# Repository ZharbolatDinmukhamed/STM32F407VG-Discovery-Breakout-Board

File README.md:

# STM32F407VG-Discovery-Breakout-Board

A shield-style adapter/breakout board for the STM32F407VG-Disc1 (Discovery) board, designed and assembled at the Tactile Laboratory, Nazarbayev University.

## Overview

This board plugs directly onto the Discovery board's P1/P2 headers and breaks out all 100 GPIO pins to individual screw terminals, making it easy to wire external hardware to the STM32F407VG without soldering directly onto the Discovery board.

## Design Details

- **Form factor:** Shield-style board, mates directly with the Discovery board's P1/P2 headers
- **Pin breakout:** All 100 pins broken out to individual screw terminals
- **Assembly:** Designed, fabricated, and hand-soldered end-to-end

## Files

- `/schematic` — Schematic source files
- `/pcb` — PCB layout files
- `/gerbers` — Fabrication-ready Gerber files
- `/images` — Board renders and photos of the assembled, soldered board

## Tools

- KiCad

## Status

Assembled and soldered

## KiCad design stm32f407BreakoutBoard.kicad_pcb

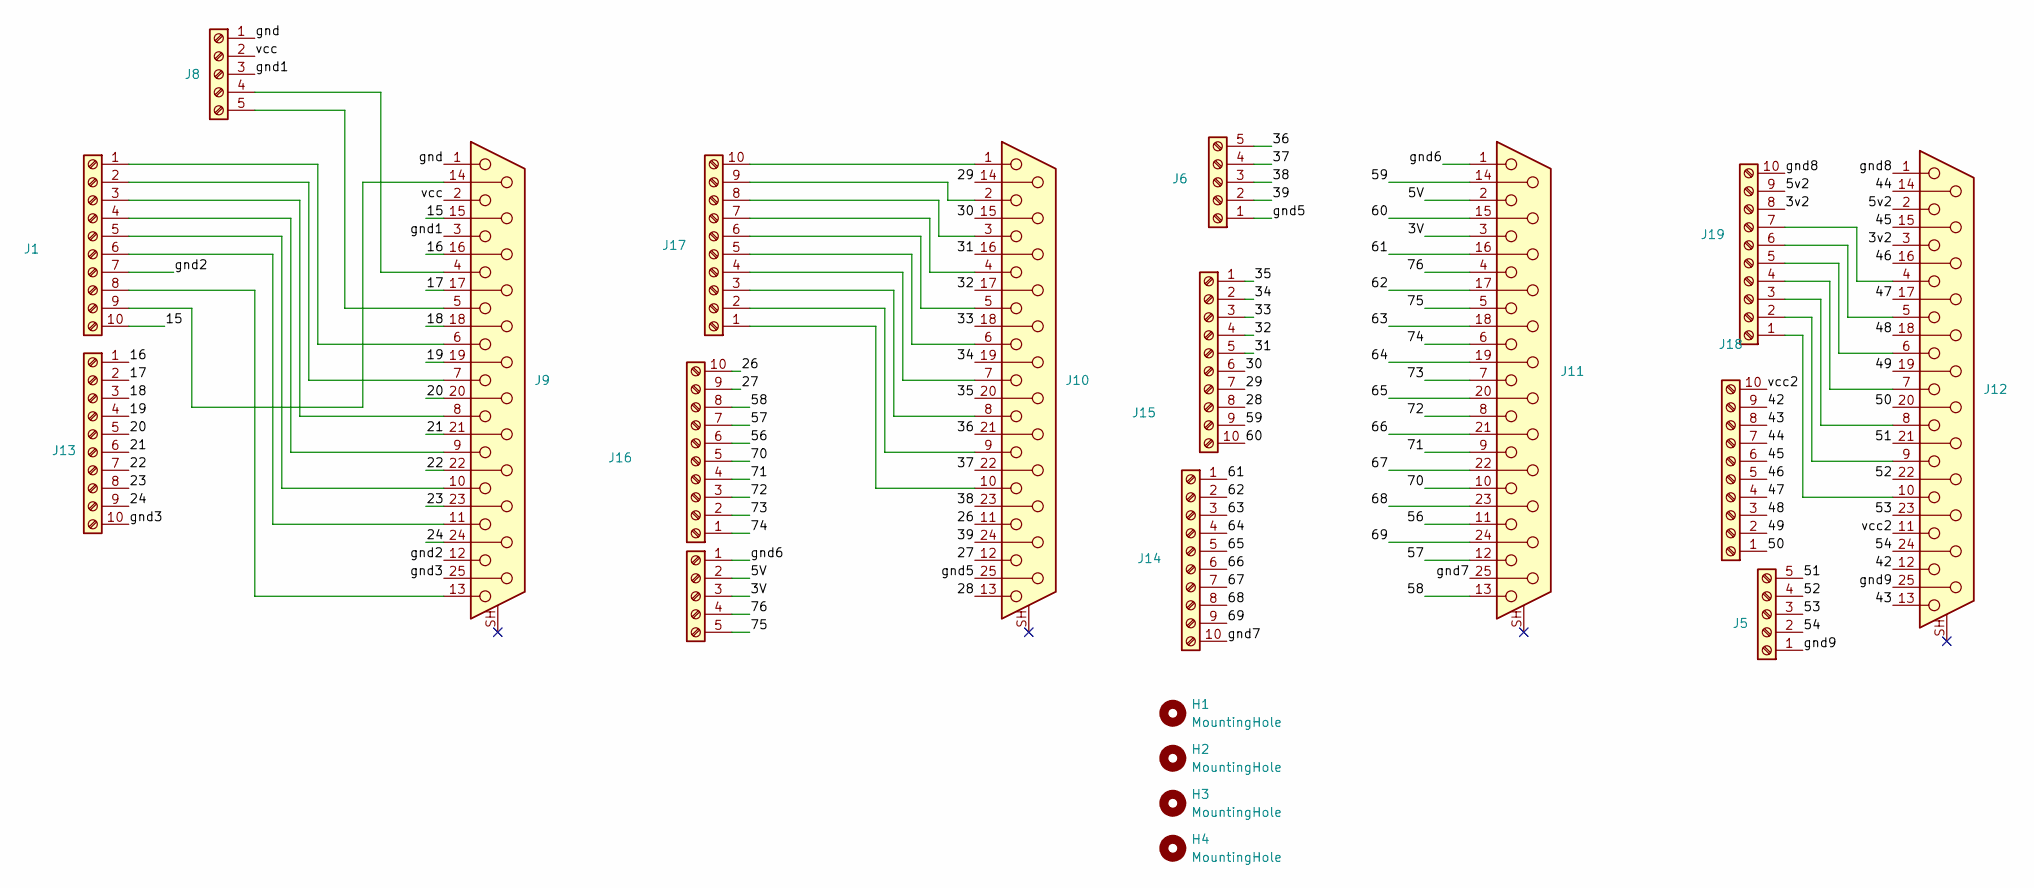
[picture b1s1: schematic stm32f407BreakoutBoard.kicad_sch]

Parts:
H1, H2, H3, H4: MountingHole; MountingHole_3.2mm_M3
J1, J13, J14, J15, J16, J17, J18, J19: Screw_Terminal_01x10; TerminalBlock_Phoenix_MKDS-1,5-10-5.08_1x10_P5.08mm_Horizon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
J5, J6, J7, J8: Screw_Terminal_01x05; TerminalBlock_Phoenix_MKDS-1,5-5-5.08_1x05_P5.08mm_Horizont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
J9, J10, J11, J12: DB25_Socket_MountingHoles; PinSocket_1x25_P2.54mm_Vertical

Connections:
/3V: J7.3, J11.3
/3v2: J12.3, J19.8
/5V: J7.2, J11.2
/5v2: J12.2, J19.9
/15: J1.10, J9.15
/16: J9.16, J13.1
/17: J9.17, J13.2
/18: J9.18, J13.3
/19: J9.19, J13.4
/20: J9.20, J13.5
/21: J9.21, J13.6
/22: J9.22, J13.7
/23: J9.23, J13.8
/24: J9.24, J13.9
/26: J10.11, J16.10
/27: J10.12, J16.9
/28: J10.13, J15.8
/29: J10.14, J15.7
/30: J10.15, J15.6
/31: J10.16, J15.5
/32: J10.17, J15.4
/33: J10.18, J15.3
/34: J10.19, J15.2
/35: J10.20, J15.1
/36: J6.5, J10.21
/37: J6.4, J10.22
/38: J6.3, J10.23
/39: J6.2, J10.24
/42: J12.12, J18.9
/43: J12.13, J18.8
/44: J12.14, J18.7
/45: J12.15, J18.6
/46: J12.16, J18.5
/47: J12.17, J18.4
/48: J12.18, J18.3
/49: J12.19, J18.2
/50: J12.20, J18.1
/51: J5.5, J12.21
/52: J5.4, J12.22
/53: J5.3, J12.23
/54: J5.2, J12.24
/56: J11.11, J16.6
/57: J11.12, J16.7
/58: J11.13, J16.8
/59: J11.14, J15.9
/60: J11.15, J15.10
/61: J11.16, J14.1
/62: J11.17, J14.2
/63: J11.18, J14.3
/64: J11.19, J14.4
/65: J11.20, J14.5
/66: J11.21, J14.6
/67: J11.22, J14.7
/68: J11.23, J14.8
/69: J11.24, J14.9
/70: J11.10, J16.5
/71: J11.9, J16.4
/72: J11.8, J16.3
/73: J11.7, J16.2
/74: J11.6, J16.1
/75: J7.5, J11.5
/76: J7.4, J11.4
/gnd: J8.1, J9.1
/gnd1: J8.3, J9.3
/gnd2: J1.7, J9.12
/gnd3: J9.25, J13.10
/gnd5: J6.1, J10.25
/gnd6: J7.1, J11.1
/gnd7: J11.25, J14.10
/gnd8: J12.1, J19.10
/gnd9: J5.1, J12.25
/vcc: J8.2, J9.2
/vcc2: J12.11, J18.10
unnamed: J1.1, J9.6
unnamed: J1.2, J9.7
unnamed: J1.3, J9.8
unnamed: J1.4, J9.9
unnamed: J1.5, J9.10
unnamed: J1.6, J9.11
unnamed: J1.8, J9.13
unnamed: J1.9, J9.14
unnamed: J8.4, J9.4
unnamed: J8.5, J9.5
unnamed: J10.10, J17.1
unnamed: J10.9, J17.2
unnamed: J10.8, J17.3
unnamed: J10.7, J17.4
unnamed: J10.6, J17.5
unnamed: J10.5, J17.6
unnamed: J10.4, J17.7
unnamed: J10.3, J17.8
unnamed: J10.2, J17.9
unnamed: J10.1, J17.10
unnamed: J12.10, J19.1
unnamed: J12.9, J19.2
unnamed: J12.8, J19.3
unnamed: J12.7, J19.4
unnamed: J12.6, J19.5
unnamed: J12.5, J19.6
unnamed: J12.4, J19.7

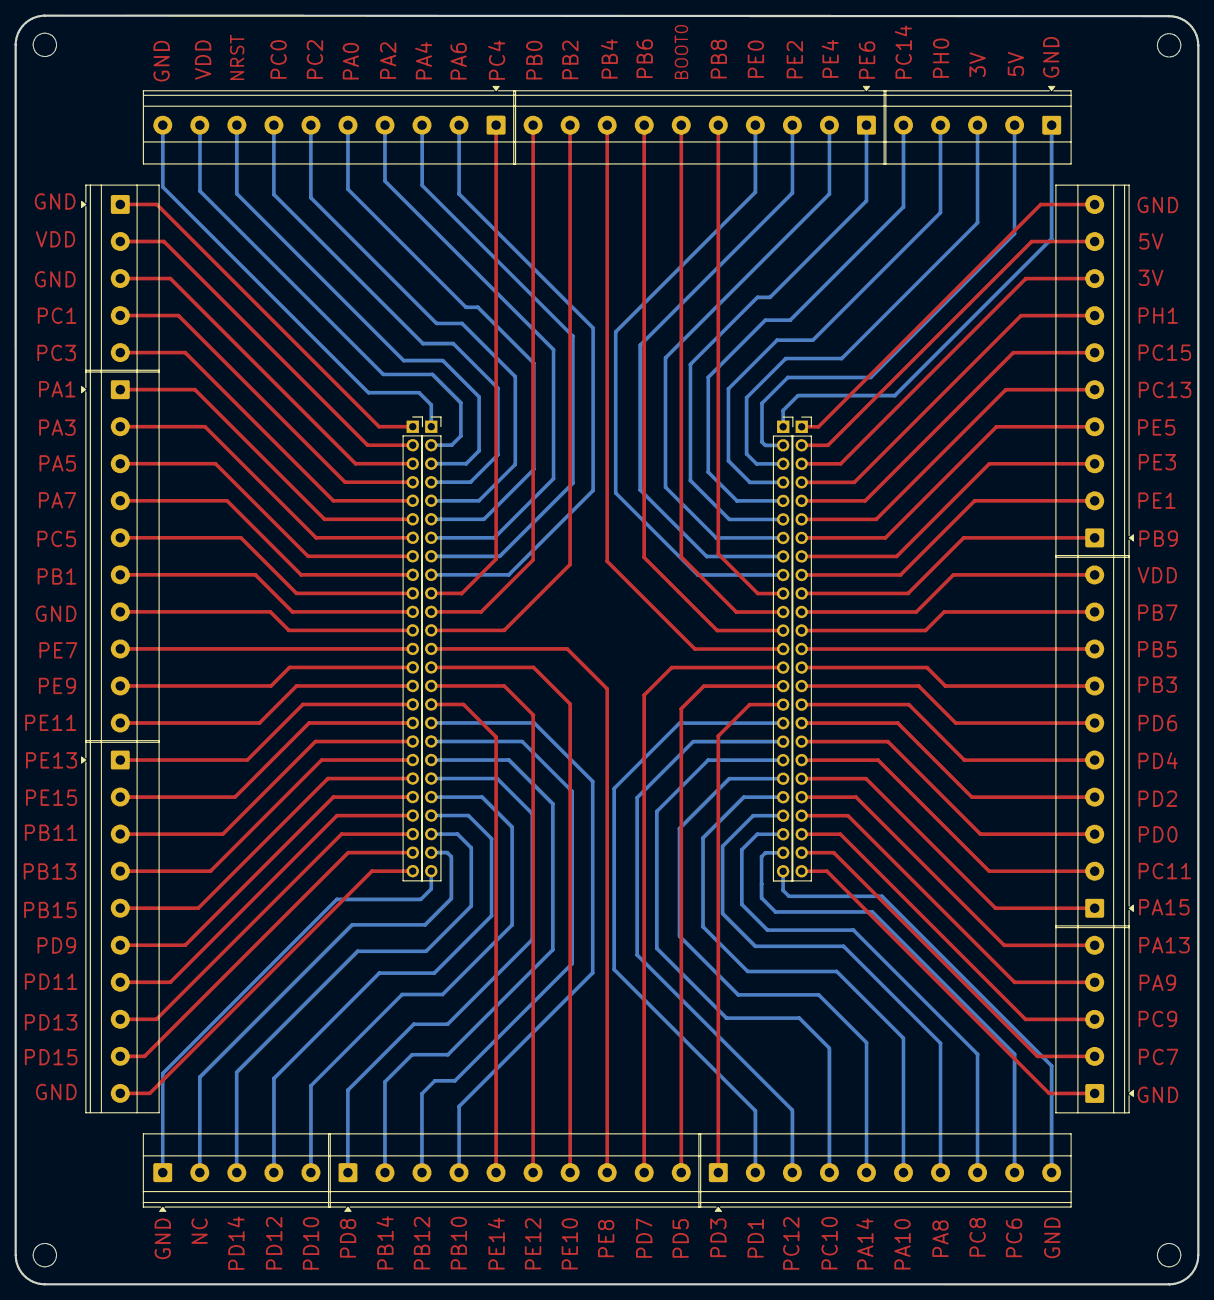
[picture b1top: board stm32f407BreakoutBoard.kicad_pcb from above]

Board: 2 copper layers, 162.2 x 174.0 mm, 20 parts (0 on the bottom side), 100 nets.
